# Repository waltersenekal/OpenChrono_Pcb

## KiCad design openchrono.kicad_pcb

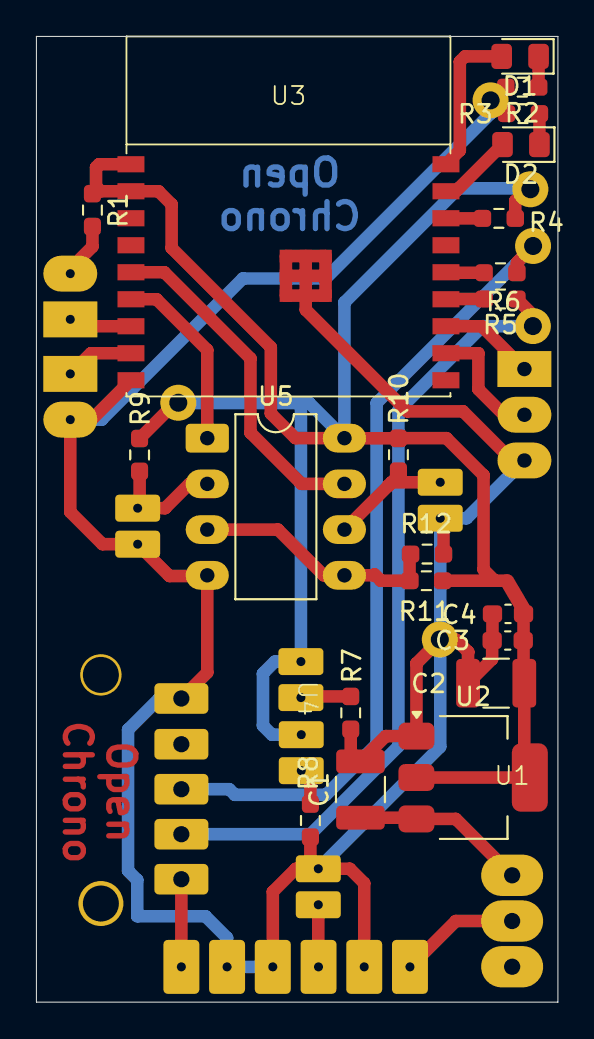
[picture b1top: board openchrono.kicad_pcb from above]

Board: 2 copper layers, 29.0 x 53.7 mm, 32 parts (0 on the bottom side), 27 nets.

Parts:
C1, C2: 10uF; C_1210_3225Metric_Pad1.33x2.70mm_HandSolder
C3: 100nF; C_0603_1608Metric_Pad1.08x0.95mm_HandSolder
C4: 10nF; C_0603_1608Metric_Pad1.08x0.95mm_HandSolder
D1, D2: LED; D_0805_2012Metric_Pad1.15x1.40mm_HandSolder
J1: Conn_01x06_Socket; SIP-6_1_2.54
J2, J4, J5, J6, J7: Conn_01x02_Socket; SIP-2_2.0
J3: SIP-3
R1, R2, R3, R4, R9, R10, R11, R12: 10K; R_0603_1608Metric_Pad0.98x0.95mm_HandSolder
R5, R6: 22R; R_0603_1608Metric_Pad0.98x0.95mm_HandSolder
R7, R8: 100R; R_0603_1608Metric_Pad0.98x0.95mm_HandSolder
SW1, SW2: SW_DIP_x01; SIP-2_1_2.54
U1: 3pin SW RA 2.54
U2: AMS1117-3.3; SOT-223-3_TabPin2
U3: ESP32-C3-WROOM-02
U4: USB Micro_Pololu_2586
U5: LM358; DIP-8_W7.62mm_LongPads

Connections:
+3.3V: C2.1, C3.1, C4.1, J4.1, J5.1, R1.1, R4.2, R9.2, R10.2, R11.2, U2.2 (VO), U3.1 (VDD_3V3), U3.2 (CHIP_EN), U5.8 (V+)
+5V: J1.1, U1.2 (COM)
+5V_IN: J1.6, U4.5 (VDD)
/Cpu/pin_Start: U3.6 (GPIO7,FSPID,MTDO), U5.1
/Cpu/pin_Stop: U3.5 (GPIO6,FSPICLK,MTCK), U5.7
/IO/USB_D+: R6.2, U3.14 (GPIO19,USB_D+)
/IO/USB_D-: R5.2, U3.13 (GPIO18,USB_D-)
GND: C1.2, C2.2, C3.2, C4.2, J1.2, J1.4, J1.5, J2.2, J3.3, J6.2, J7.2, R2.2, R3.2, R7.1, R8.1, R12.1, SW2.2, U2.1 (GND), U3.9 (GND), U3.19, U3.20, U3.21, U3.22, U3.23, U3.24, U3.25, U3.26, U3.27, U4.1 (GND), U5.4 (V-)
unnamed: D1.2 (A), U3.18 (GPIO0,ADC1_CH0,XTAL_32K_P)
unnamed: D1.1 (K), R2.1
unnamed: D2.2 (A), U3.17 (GPIO1,ADC1_CH1,XTAL_32K_N)
unnamed: D2.1 (K), R3.1
unnamed: J4.2, R7.2
unnamed: J5.2, R8.2
unnamed: J6.1, R9.1, U5.2 (-)
unnamed: J7.1, R10.1, U5.6 (-)
unnamed: R1.2, SW1.2
unnamed: C1.1, U1.1 (NO), U2.3 (VI)
unnamed: R4.1, U3.16 (GPIO2,ADC1_CH2,FSPIQ)
unnamed: SW1.1, U3.7 (GPIO8)
unnamed: SW2.1, U3.8 (GPIO9)
unnamed: J3.2, U3.11 (GPIO20,U0RXD)
unnamed: J3.1, U3.12 (GPIO21,U0TXD)
unnamed: R6.1, U4.3 (D+)
unnamed: R5.1, U4.4 (D-)
unnamed: R11.1, R12.2, U5.3 (+), U5.5 (+)
VBatt: J1.3, J2.1

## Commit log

2025-04-25 PCB V1
2025-04-25 Added my 3d adapter for my pellet gun
